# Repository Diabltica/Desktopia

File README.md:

# Desktopia

Desktopia is an open-source project for easy height control of your IKEA Skarsta/Trotten sit-stand desk, providing a
comfortable and customizable workspace experience.

A DC motor replaces the crank handle. Two boards control it: the **motherboard** under the desk top, and the **HMI board**
on the front edge with a round screen and five buttons. A time-of-flight sensor measures the desk height, so the desk can
go back to three saved heights at the press of a button.

## How it works

```mermaid
flowchart LR
    PSU[24 V power supply] -->|J1| MB
    subgraph MB[Motherboard - ATmega32U4]
        direction TB
        SHUNT[2 mΩ shunt + INA226]
        SW[P-MOSFET supply switch]
        TOF[VL53L1CB height sensor]
    end
    MB -->|J5: switched 24 V| DRV[Cytron MD10C motor driver]
    MB -->|J6: DIR + PWM + GND| DRV
    DRV --> MOTOR[Motor] --> GEAR[Gearbox] --> DESK[Desk]
    MB <-->|RJ11 cord: 5 V + RS-485| HMI[HMI board - RP2040<br/>round screen + 5 buttons]
```

- The **motherboard** makes every decision. It reads the height (VL53L1CB), runs the state machine, drives the motor
  driver (direction + PWM, with ramps) and stores the presets in its EEPROM. It also switches the driver's 24 V supply:
  on for a move, off after 5 minutes without one, and off at once if the motor current goes over the limit (INA226).
- The **HMI board** only displays what the motherboard sends and reports the button levels. It is powered by the
  motherboard through the RJ11 cord, which also carries the RS-485 link (250 kbaud, polled every 10 ms).
- If the cord, the sensor or the firmware fails, or the motor draws too much current, the motor stops: see the protections in
  [firmware/README.md](firmware/README.md#built-in-protections).

## Usage

| Action | Result |
|---|---|
| **Up / Down** held | the desk moves as long as the button is held |
| **Preset 1-3**, short press | the desk goes to the saved height |
| **Preset 1-3**, long press (2 s) | the current height is saved |
| any button during an automatic move | stop |

## Repository layout

| Folder | Content | Documentation |
|---|---|---|
| [hardware/desktopia/](hardware/desktopia/) | motherboard KiCad project (schematic, PCB) | [README](hardware/desktopia/README.md) |
| [hardware/desktopia_HMI/](hardware/desktopia_HMI/) | HMI board KiCad project (schematic, PCB) | [README](hardware/desktopia_HMI/README.md) |
| [hardware/kicad_library/](hardware/kicad_library/) | symbols and footprints shared by both KiCad projects (`JLCImport`, ...) | |
| [hardware/render.sh](hardware/render.sh) | renders the schematic / PCB / 3D images of the board READMEs; run by the [*Hardware images*](.github/workflows/hardware-images.yml) workflow on every push | |
| [firmware/desktopia/](firmware/desktopia/) | motherboard firmware (ATmega32U4, PlatformIO) | [README](firmware/desktopia/README.md) |
| [firmware/desktopia_HMI/](firmware/desktopia_HMI/) | HMI board firmware (RP2040, PlatformIO) | [README](firmware/desktopia_HMI/README.md) |
| [firmware/shared/hmi_link/](firmware/shared/hmi_link/) | link protocol and screen model, compiled into both firmwares | [hmi_protocol.h](firmware/shared/hmi_link/hmi_protocol.h) |
| [firmware/sim/](firmware/sim/) | PC simulation of both boards from their real sources (Linux / WSL) | [README](firmware/README.md#simulation-bench-optional) |
| [mechanical/](mechanical/) | 3D-printed motor supports with silent blocks and jaw coupling (CadQuery scripts, STL / STEP, assembly report) | [README](mechanical/README.md) |
| [documentation/](documentation/) | VL53L1X datasheet | |

## Getting started

Tools: [KiCad 10](https://www.kicad.org/) for the boards, [PlatformIO](https://platformio.org/) for the firmwares.

1. **Boards**: open each KiCad project, update the PCB from the schematic and order it. Every assembled part has its
   JLCPCB / LCSC number in the `LCSC` field. Read the board READMEs first: both PCBs still have to be updated after
   the latest schematic changes.
2. **HMI firmware**: `cd firmware/desktopia_HMI && pio run -t upload` with the board in USB boot mode.
3. **Motherboard firmware**: `cd firmware/desktopia && pio run -t upload` (the board must be powered from its 24 V input).
4. **First power-up**: follow [the checklist](firmware/README.md#first-power-up-do-it-in-this-order), with the motor
   decoupled from the desk at first.

The firmware of both boards can be tested on a PC without any hardware (`firmware/sim/`, Linux / WSL).

## Status

- Firmwares: build with no warnings; tested in the PC simulation only.
- Schematics: ERC checked, netlists checked by script.
- PCBs: **not yet updated** to the latest schematics (RJ11 link, RP2040 HMI board, power input, current sensor, motor supply switch).
- Nothing has been tested on real boards yet.

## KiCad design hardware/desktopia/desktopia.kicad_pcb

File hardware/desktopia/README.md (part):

# Desktopia – motherboard

KiCad 10 project: `desktopia.kicad_sch`, `desktopia.kicad_pcb`. Firmware: [../../firmware/desktopia/](../../firmware/desktopia/README.md).

The motherboard sits under the desk top. It takes the 24 V supply and passes it through a current shunt and a MOSFET
switch to its own H-bridge (DRV8701E gate driver, four N-MOSFETs), which drives the motor. The bridge can be bypassed:
J5 / J6 still give the switched 24 V and DIR / PWM to an external driver. The board measures the height, powers the HMI
board and talks to it.

## Views

Interactive viewer (KiCanvas, opens the files of the `main` branch in the browser):
[schematic](https://kicanvas.org/?github=https://github.com/Diabltica/Desktopia/blob/main/hardware/desktopia/desktopia.kicad_sch) · [PCB](https://kicanvas.org/?github=https://github.com/Diabltica/Desktopia/blob/main/hardware/desktopia/desktopia.kicad_pcb).

The images below are rendered by [`../render.sh`](../render.sh) and committed by the
[*Hardware images*](../../.github/workflows/hardware-images.yml) workflow on every push that touches `hardware/`.
Click an image to open it full size.
The 3D view shows the plugs of J1 / J5 / J6 / J7 in their headers: the `Desktopia:PluggableHeader_*` footprints carry
KiCad's Phoenix Contact header model and a plug generated by
[`pluggable_plug_3d.py`](../kicad_library/pcb/tools/pluggable_plug_3d.py) (the footprints by
[`pluggable_header_fp.py`](../kicad_library/pcb/tools/pluggable_header_fp.py)).

Reading the schematic: connections are drawn as wires. A label only appears where a net leaves one block for another,
at the MCU pin and at the block it reaches (`TOF_INT`, `SCL`, `SDA`, `Mpwm`, `Mdir`, `nSLEEP`, `nFAULT`, `MOTOR_PWR`,
`I_ALERT`, `RESET`, `+5V_HMI`, `MOTOR_SW`). `MOTOR_24V` only names a 15 A net. In the H-bridge block, `OUT1` / `OUT2`
join the two legs to J7, `LS_SRC` joins the low-side sources to the shunts R27 / R28 under U7, and `VM` names the
bridge supply after JP6. Wires that cross without a dot are not connected: MISO over SCK / MOSI at J2, D+ over D- at
the USB connector, Vin+ over Vin- at the INA226, DI over DE at U5.

Colours: each block has its own background and title colour (24 V input and 5 V supply, MCU, height sensor, HMI link,
motor supply, H-bridge). Wires and labels take the colour of their net class, with a legend on the sheet, left of the
MCU:

| Colour | Net class | Nets |
|---|---|---|
| red, thick | `Power_24V` | `+24V`, `MOTOR_24V`, `MOTOR_SW`, `VM`, `OUT1` / `OUT2`, `LS_SRC`: the 15 A path |
| orange | `Power_5V` | `+5V`, `+5V_HMI` |
| purple | `Power_2V8` | `+2V8` |
| grey | `GND` | `GND` |
| blue | `Motor_command` | `Mdir`, `Mpwm`, `nSLEEP`, `nFAULT`, `MOTOR_PWR`, `I_ALERT`, and PH / EN / nSLEEP / nFAULT after JP2-JP5 |
| magenta | `Gate_drive` | the four gates of the H-bridge |
| brown | `Current_sense` | Kelvin lines: Vin+ / Vin- of the INA226, SP / SN of the DRV8701 |
| teal | `Buses` | I2C (both sides of Q1 / Q2), ToF interrupt, RS-485, USB D+ / D- |
| green | `Default` | everything else |
| green (PCB only) | `HV_signal`, `Switch_node` | 24-38 V low-current nets (charge pump, bootstrap, Q5 gate), TPS5430 switch node |

The classes and their net patterns are in the project settings (*Schematic Setup → Net Classes*). Unnamed nets are
matched by their KiCad name (`Net-(Q6-G)`...): after renaming one of these parts, update its pattern. Each class also
sets the PCB track width, clearance and via: see *PCB rules*.

**Schematic**

**PCB**

| Front | Back (mirrored) |
|---|---|
|  |  |

**3D**

| Top | Bottom |
|---|---|
|  |  |

## Blocks

| Block | Parts | Notes |
|---|---|---|
| 24 V input | J1 (5.08 mm pluggable terminal, 15 A), D2 SMBJ28A (600 W TVS), C6 (100 µF 50 V bulk), C5 (10 µF 50 V ceramic), TP5 | J1 carries the full motor current. D2 clamps motor and hot-plug spikes below the 40 V absolute maximum of U2 and U6 |
| 24 V → 5 V | U2 TPS5430 (3 A buck), L1 22 µH (1.8 A, shielded), D1 SS34 (3 A), C3 10 nF (boot), C7 + C8 (2 × 47 µF ceramic), R4 / R7 (10k / 3.3k → 4.92 V), C4 / R9 / C12 / C11 (compensation) | 1.5 A available. ENA left open, see *Known issues* |
| Motor current | R23 2 mΩ 3 W shunt, U6 INA226 (I2C 0x40), C22, R25, C23 | ±41 A full scale; alert on PE6 / INT6 (R25 4.7k pull-up, C23 100 pF against motor spikes). The firmware cuts the PWM and Q5 on an alert |
| Motor supply switch | Q5 IPD90P04P4-05 (P-MOSFET, −40 V, 4.7 mΩ, TO-252), Q4 BSS138 (gate driver), R21 / R20 100k (gate divider), R22 10k (pull-down), D3 BZT52C15 (V<sub>GS</sub> clamp), C21 100 nF 50 V (soft start), D4 SS34, TP13 | no relay. `MOTOR_PWR` (PD7) high → Q4 on → V<sub>GS</sub> −12 V → J5 powered. R22 keeps it off while the MCU is in reset or blank. See *Power* |
| MCU | U4 ATmega32U4 @ 16 MHz (Y1, C15 / C16), RST1 reset button, R12 reset pull-up | Caterina bootloader, USB. HWB (PE2) is not connected: the Leonardo fuses leave HWBE off |
| USB | J3 USB-C (G-Switch GT-USB-7010ASV), R13 / R15 22 Ω, R18 / R19 5.1k on CC | VBUS only goes to the MCU's VBUS sense pin: USB does **not** power the board |
| ISP | J2 2×3 header (not assembled) | blank chip: bootloader + fuses with a USBasp |
| Height sensor | U3 VL53L1CB, U1 XC6206P282 (2.8 V LDO), Q1 / Q2 / Q3 BSS138 (5 V ↔ 2.8 V level shifters: SCL, SDA, GPIO1), R2 / R6 / R8 / R11, R10 | XSHUT tied high (R8). GPIO1 (data ready) reaches PB4 / PCINT4 as `TOF_INT` |
| Motor command | J5 (switched 24 V out, `MOTOR_SW`), J6 (DIR, PWM, GND), R26 / R24 (10k pull-downs on PWM / DIR) | DIR / PWM go to the on-board H-bridge, and to J6 for an external driver (Cytron MD10C R3) when the bridge is bypassed. The pull-downs keep the motor stopped while the MCU is in reset, in the bootloader or blank |
| H-bridge | U7 DRV8701E (gate driver, PH/EN), Q6 / Q7 / Q8 / Q9 BSC028N06NS (60 V, 2.8 mΩ, SuperSO8), C24 / C25 (2 × 470 µF 50 V low impedance), C26 / C27 (10 µF 50 V), C28 (100 nF, VM), C29 (VCP), C30 (charge pump), C31 / C32 (AVDD / DVDD), R27 / R28 (2 × 2 mΩ 3 W shunt, Kelvin), R29 / R30 (VREF divider), TP14 (SO), J7 (motor), JP2-JP5 (solder jumpers), JP6 (wire link) | PH = `Mdir`, EN = `Mpwm` (up to 100 kHz, 25 kHz planned). EN low = brake. `nSLEEP` (PB5) low = bridge off, `nFAULT` (PB7) = fault. Current limited cycle by cycle at about 14.6 A. See *H-bridge* |
| HMI link | J4 RJ11 6P6C, U5 SP485EEN (RS-485), F1 500 mA PTC, R14 / R17 4.7k bias, R16 120 Ω (not assembled), C18 / C20 | see the link section of the firmware README |
| Power LED | LED1, R3 (470 Ω, 6 mA), JP1 solder jumper | LED off until JP1 is bridged |

## Connectors

| Ref | Function | Pin-out |
|---|---|---|
| J1 | 24 V supply input | 1 = +24 V, 2 = GND |
| J2 | ISP | 1 = MISO, 2 = +5 V, 3 = SCK, 4 = MOSI, 5 = RESET, 6 = GND |
| J3 | USB-C: flashing and debug logs | USB 2.0 full speed |
| J4 | RJ11 cord to the HMI board | 1 = +5 V, 2 = GND, 3 = A, 4 = B, 5 = GND, 6 = +5 V |
| J5 | supply out to an external motor driver (after the shunt and Q5) | 1 = MOTOR_SW, 2 = GND |
| J6 | external motor driver command | 1 = DIR (`Mdir`, PC6), 2 = PWM (`Mpwm`, PB6 / OC1B), 3 = GND (the driver's logic ground) |
| J7 | motor, from the on-board H-bridge | 1 = OUT1 (Q6 / Q7), 2 = OUT2 (Q8 / Q9) |

The J4 pin-out is symmetric, so a reversed telephone cord only swaps A and B, never +5 V and GND. The HMI firmware
detects and corrects the swap. Use 6-conductor (6P6C) cords only, and never plug J4 into a telephone wall socket.

The four terminals unplug. The board has the header; the wires are screwed into a plug, so the board can be fitted or
removed without touching a screw under the desk. JLCPCB solders the headers; buy the plugs with the parts (LCSC), they
are not in the assembly BOM. Each header carries its plug in the `Plug` field of the schematic.

| Ref | Header (on the board) | Plug (on the cable) | Rating | Wire |
|---|---|---|---|---|
| J1, J5 | Cixi Kefa KF2EDGRC-5.08-2P (C441236), 5.08 mm, right angle, closed ends | KF2EDGK-5.08-2P-AA (C440880) | 15 A, 300 V | up to 2.5 mm² (12 AWG) |
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
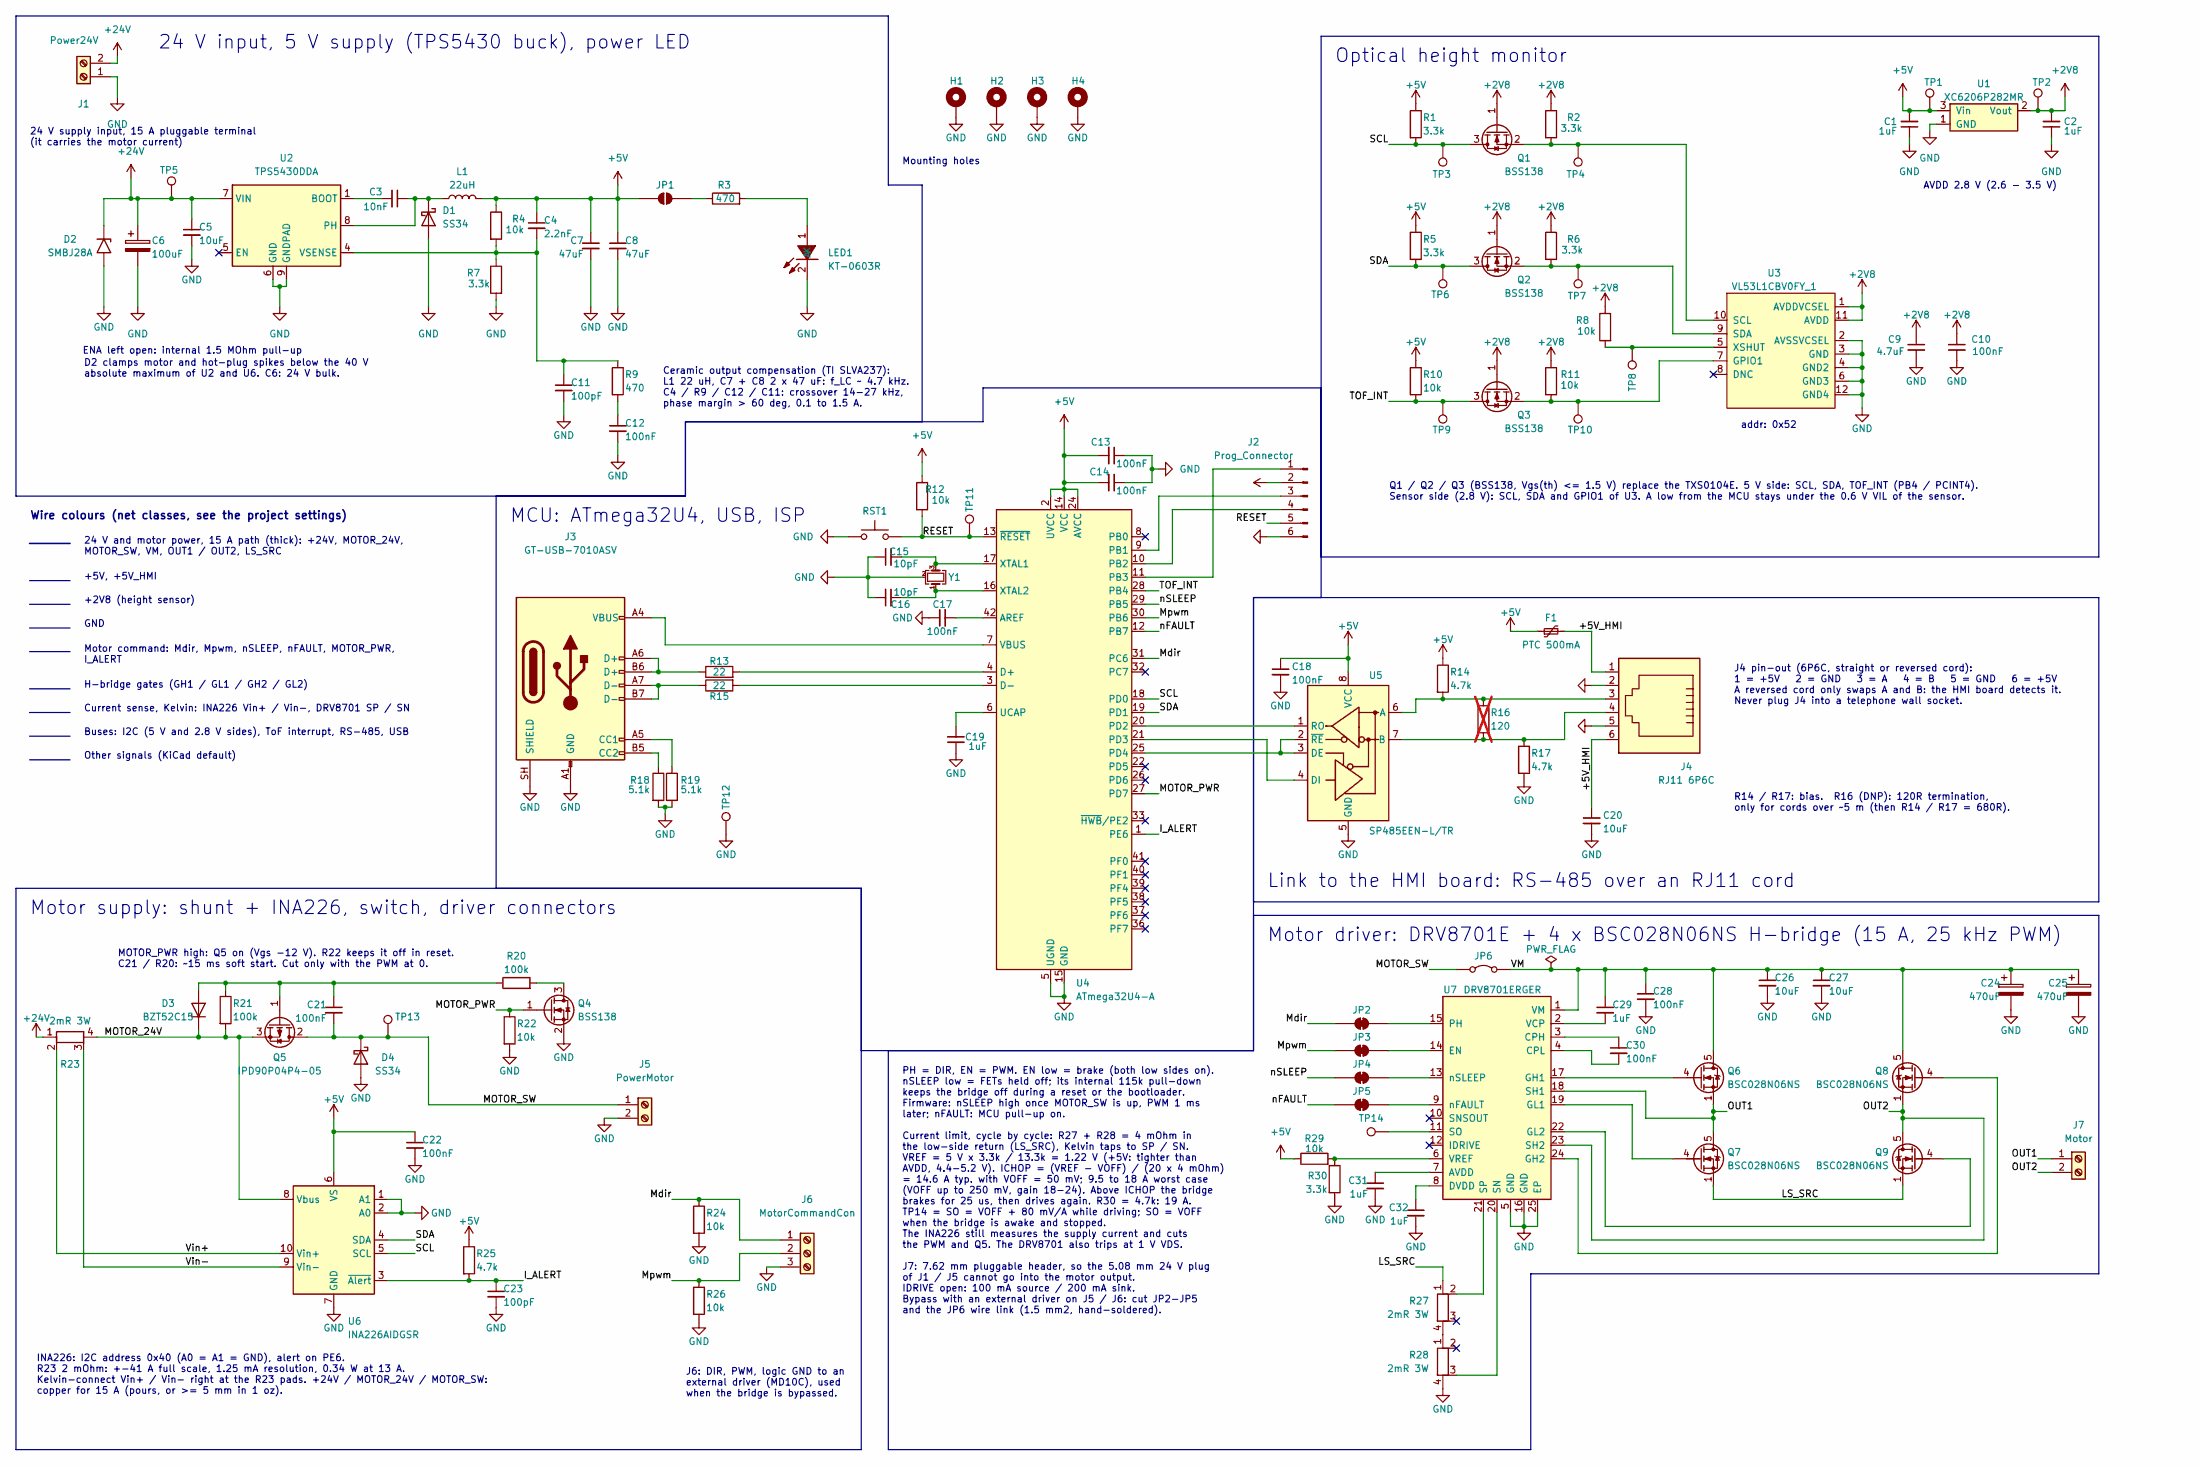
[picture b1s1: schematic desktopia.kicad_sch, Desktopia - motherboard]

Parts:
C1, C2, C19, C29, C31, C32: 1uF; C_0402_1005Metric; jlcpcb PartNumber C52923
C3: 10nF; C_0402_1005Metric; jlcpcb PartNumber C15195
C4: 2.2nF; C_0603_1608Metric; Manufacturer Part 0603B222K500NT; LCSC C1604
C5, C26, C27: 10uF; C_1206_3216Metric; Voltage 50V X5R; LCSC C13585
C6: 100uF; CP_Elec_8x10; Voltage 50V; Manufacturer Part RVT1H101M0810; LCSC C970687
C7, C8: 47uF; C_1206_3216Metric; Voltage 10V X5R; Manufacturer Part CL31A476MPHNNNE; LCSC C96123
C9: 4.7uF; C_0402_1005Metric; jlcpcb PartNumber C23733
C10, C13, C14, C17, C18: 100nF; C_0402_1005Metric; jlcpcb PartNumber C1525
C11, C23: 100pF; C_0402_1005Metric; Manufacturer Part 0402CG101J500NT; LCSC C1546
C12: 100nF; C_0402_1005Metric; Manufacturer Part CL05B104KO5NNNC; LCSC C1525
C15, C16: 10pF; C_0402_1005Metric; jlcpcb PartNumber C32949
C20: 10uF; C_0603_1608Metric; jlcpcb PartNumber C19702
C21, C28, C30: 100nF; C_0402_1005Metric; Voltage 50V X7R; Manufacturer Part CL05B104KB54PNC; LCSC C307331
C22: 100nF; C_0402_1005Metric; LCSC C1525
C24, C25: 470uF; CP_Radial_D10.0mm_P5.00mm; Voltage 50V; Manufacturer Part 50ZLJ470M10X20; LCSC C2902875
D1: SS34; D_SMA; jlcpcb PartNumber C8678
D2: SMBJ28A; D_SMB; Manufacturer Part SMBJ28A; LCSC C19077582
D3: BZT52C15; D_SOD-123; Manufacturer Part BZT52C15; LCSC C19077412
D4: SS34; D_SMA; Manufacturer Part SS34; LCSC C8678
F1: PTC 500mA; Fuse_1206_3216Metric; LCSC C720075
H1, H2, H3, H4: MountingHole_Pad; MountingHole_2.2mm_M2_Pad
J1: Power24V; PluggableHeader_2EDGRC_1x02_P5.08mm_Horizontal; Manufacturer Part KF2EDGRC-5.08-2P; LCSC C441236
J2: Prog_Connector; IDC-Header_2x03_P2.54mm_Vertical
J3: GT-USB-7010ASV; USB_C_Receptacle_G-Switch_GT-USB-7010ASV; Manufacturer Part GT-USB-7010ASV; LCSC C2988369
J4: RJ11 6P6C; RJ12_Amphenol_54601-x06_Horizontal; LCSC C3097716
J5: PowerMotor; PluggableHeader_2EDGRC_1x02_P5.08mm_Horizontal; Manufacturer Part KF2EDGRC-5.08-2P; LCSC C441236
J6: MotorCommandCon; PluggableHeader_15EDGRC_1x03_P3.81mm_Horizontal; Manufacturer Part WJ15EDGRC-3.81-03P-14-00A; LCSC C8406
J7: Motor; PluggableHeader_2EDGRC_1x02_P7.62mm_Horizontal; Manufacturer Part KF2EDGRC-7.62-2P; LCSC C441246
JP1: SolderJumper_2_Open; SolderJumper-2_P1.3mm_Open_TrianglePad1.0x1.5mm
JP2, JP3, JP4, JP5: SolderJumper_2_Bridged; SolderJumper-2_P1.3mm_Bridged_RoundedPad1.0x1.5mm
JP6: 1.5 mm2 wire; SolderWire-1.5sqmm_1x02_P6mm_D1.7mm_OD3mm
L1: 22uH; L_Sunlord_SWPA6045S; Manufacturer Part SWPA6045S220MT; jlcpcb PartNumber C83454
LED1: KT-0603R; Manufacturer Part KT-0603R; LCSC C2286
Q1, Q2, Q3, Q4: BSS138; SOT-23; Manufacturer Part BSS138; LCSC C7420339
Q5: IPD90P04P4-05; TO-252-2; Manufacturer Part IPD90P04P405; LCSC C536914
Q6, Q7, Q8, Q9: BSC028N06NS; TDSON-8-1; Manufacturer Part BSC028N06NSATMA1; LCSC C148250
R1, R2, R5, R6, R7, R30: 3.3k; R_0402_1005Metric; jlcpcb PartNumber C25890
R3: 470; R_0402_1005Metric; jlcpcb PartNumber C25117
R4, R8, R11, R12: 10k; R_0402_1005Metric; jlcpcb PartNumber C25744
R9: 470; R_0402_1005Metric; Manufacturer Part 0402WGF4700TCE; LCSC C25117
R10, R22, R24, R26, R29: 10k; R_0402_1005Metric; Manufacturer Part 0402WGF1002TCE; LCSC C25744
R13, R15: 22; R_0402_1005Metric; jlcpcb PartNumber C25092
R14, R17: 4.7k; R_0402_1005Metric; jlcpcb PartNumber C25900
R16: 120; R_0402_1005Metric; jlcpcb PartNumber C25079; not fitted
R18, R19: 5.1k; R_0402_1005Metric; jlcpcb PartNumber C25905
R20, R21: 100k; R_0402_1005Metric; Manufacturer Part 0402WGF1003TCE; LCSC C25741
R23, R27, R28: 2mR 3W; R_2512_CurrentSensing_opti; LCSC C154685
R25: 4.7k; R_0402_1005Metric; LCSC C25900
RST1: TS-1088-AR02016; SW_SPST_TS-1088-xR020; LCSC C720477
TP1, TP2, TP3, TP4, TP5, TP6, TP7, TP8, TP9, TP10, TP11, TP12, TP13, TP14: TestPoint; TestPoint_Pad_D1.0mm
U1: XC6206P282MR; SOT-23-3; Manufacturer Part XC6206P282MR; LCSC C347374
U2: TPS5430DDA; TI_SO-PowerPAD-8_ThermalVias; jlcpcb PartNumber C9864
U3: VL53L1CBV0FY_1; Manufacturer Part VL53L1CBV0FY/1; LCSC C2970716
U4: ATmega32U4-A; TQFP-44_10x10mm_P0.8mm; LCSC C44854
U5: SP485EEN-L/TR; SOIC-8_3.9x4.9mm_P1.27mm; LCSC C6855
U6: INA226AIDGSR; TSSOP-10_3x3mm_P0.5mm; LCSC C49851
U7: DRV8701ERGER; Texas_RGE0024H_VQFN-24-1EP_4x4mm_P0.5mm_EP2.7x2.7mm_Thermal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; Manufacturer Part DRV8701ERGER; LCSC C90964
Y1: X322516MLB4SI; Crystal_SMD_3225-4Pin_3.2x2.5mm; jlcpcb PartNumber C13738

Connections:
+2V8: C2.2, C9.1, C10.1, Q1.1 (G), Q2.1 (G), Q3.1 (G), R2.1, R6.1, R8.1, R11.1, TP2.1 (1_1), U1.2 (Vout), U3.1 (AVDDVCSEL), U3.11 (AVDD)
+5V: C1.2, C4.1, C7.1, C8.1, C13.2, C14.2, C18.1, C22.1, F1.1, J2.2, JP1.1 (A), L1.2, R1.1, R4.1, R5.1, R10.1, R12.1, R14.1, R25.1, R29.1, TP1.1 (1_1), U1.3 (Vin), U4.2 (UVCC), U4.14 (VCC), U4.24 (AVCC), U4.34 (VCC), U4.44 (AVCC), U5.8 (VCC), U6.6 (VS)
+24V: C5.1, C6.1, D2.1 (A1), J1.2, R23.1, TP5.1 (1_1), U2.7 (VIN)
/+5V_HMI: C20.1, F1.2, J4.1, J4.6
/I_ALERT: C23.1, R25.2, U4.1 (PE6), U6.3 (~Alert)
/LS_SRC: Q7.1 (S), Q7.2 (S), Q7.3 (S), Q9.1 (S), Q9.2 (S), Q9.3 (S), R27.1
/MOTOR_24V: D3.1 (K), Q5.3 (S), R21.2, R23.4, U6.8 (Vbus)
/MOTOR_PWR: Q4.1 (G), R22.1, U4.27 (PD7)
/MOTOR_SW: C21.2, D4.1 (K), J5.1, JP6.1 (A), Q5.2 (D), TP13.1 (1_1)
/Mdir: J6.1, JP2.1 (A), R24.1, U4.31 (PC6)
/Mpwm: J6.2, JP3.1 (A), R26.1, U4.30 (PB6)
/OUT1: J7.1, Q6.1 (S), Q6.2 (S), Q6.3 (S), Q7.5 (D), U7.18 (SH1)
/OUT2: J7.2, Q8.1 (S), Q8.2 (S), Q8.3 (S), Q9.5 (D), U7.23 (SH2)
/RESET: J2.5, R12.2, RST1.2, TP11.1 (1_1), U4.13 (~RESET)
/SCL: Q1.3 (D), R1.2, TP3.1 (1_1), U4.18 (PD0), U6.5 (SCL)
/SDA: Q2.3 (D), R5.2, TP6.1 (1_1), U4.19 (PD1), U6.4 (SDA)
/TOF_INT: Q3.3 (D), R10.2, TP9.1 (1_1), U4.28 (PB4)
/Vin+: R23.2, U6.10 (Vin+)
/Vin-: R23.3, U6.9 (Vin-)
/nFAULT: JP5.1 (A), U4.12 (PB7)
/nSLEEP: JP4.1 (A), U4.29 (PB5)
GND: C1.1, C2.1, C5.2, C6.2, C7.2, C8.2, C9.2, C10.2, C11.2, C12.2, C13.1, C14.1, C15.1, C16.1, C17.1, C18.2, C19.1, C20.2, C22.2, C23.2, C24.2, C25.2, C26.2, C27.2, C28.2, C31.2, C32.2, D1.2 (A), D2.2 (A2), D4.2 (A), H1.1 (1_1), H2.1 (1_1), H3.1 (1_1), H4.1, J1.1, J2.6, J3.A1 (GND), J3.A12 (GND), J3.B1 (GND), J3.B12 (GND), J3.SH (SHIELD), J4.2, J4.5, J5.2, J6.3, LED1.2 (K), Q4.2 (S), R7.2, R17.2, R18.2, R19.2, R22.2, R24.2, R26.2, R28.4, R30.2, RST1.1, TP12.1 (1_1), U1.1 (GND), U2.6 (GND), U2.9 (GNDPAD), U3.2 (AVSSVCSEL), U3.3 (GND), U3.4 (GND2), U3.6 (GND3), U3.12 (GND4), U4.5 (UGND), U4.15 (GND), U4.23 (GND), U4.35 (GND), U4.43 (GND), U5.5 (GND), U6.1 (A1), U6.2 (A0), U6.7 (GND), U7.5 (GND), U7.16 (GND), U7.25 (EP), Y1.2 (G), Y1.4 (G)
unnamed: C12.1, R9.2
unnamed: C3.1, D1.1 (K), L1.1, U2.8 (PH)
unnamed: C21.1, D3.2 (A), Q5.1 (G), R20.1, R21.1
unnamed: J2.1, U4.11 (PB3)
unnamed: J2.3, U4.9 (PB1)
unnamed: J2.4, U4.10 (PB2)
unnamed: J3.A5 (CC1), R19.1
unnamed: J3.B5 (CC2), R18.1
unnamed: J3.A6 (D+), J3.B6 (D+), R13.1
unnamed: J3.A7 (D-), J3.B7 (D-), R15.1
unnamed: JP1.2 (B), R3.1
unnamed: JP2.2 (B), U7.15 (PH)
unnamed: JP3.2 (B), U7.14 (EN)
unnamed: JP4.2 (B), U7.13 (nSLEEP)
unnamed: JP5.2 (B), U7.9 (nFAULT)
unnamed: C24.1, C25.1, C26.1, C27.1, C28.1, C29.1, JP6.2 (B), Q6.5 (D), Q8.5 (D), U7.1 (VM)
unnamed: LED1.1 (A), R3.2
unnamed: Q1.2 (S), R2.2, TP4.1 (1_1), U3.10 (SCL)
unnamed: Q2.2 (S), R6.2, TP7.1 (1_1), U3.9 (SDA)
unnamed: Q3.2 (S), R11.2, TP10.1 (1_1), U3.7 (GPIO1)
unnamed: Q4.3 (D), R20.2
unnamed: Q6.4 (G), U7.17 (GH1)
unnamed: Q7.4 (G), U7.19 (GL1)
unnamed: Q8.4 (G), U7.24 (GH2)
unnamed: Q9.4 (G), U7.22 (GL2)
unnamed: R27.4, R28.1
unnamed: C3.2, U2.1 (BOOT)
unnamed: C4.2, C11.1, R4.2, R7.1, R9.1, U2.4 (VSENSE)
unnamed: R8.2, TP8.1 (1_1), U3.5 (XSHUT)
unnamed: C17.2, U4.42 (AREF)
unnamed: R13.2, U4.4 (D+)
unnamed: R15.2, U4.3 (D-)
unnamed: U4.20 (PD2), U5.1 (RO)
unnamed: U4.21 (PD3), U5.4 (DI)
unnamed: U4.25 (PD4), U5.2 (~RE), U5.3 (DE)
unnamed: C19.2, U4.6 (UCAP)
unnamed: J3.A4 (VBUS), J3.A9 (VBUS), J3.B4 (VBUS), J3.B9 (VBUS), U4.7 (VBUS)
unnamed: C15.2, U4.17 (XTAL1), Y1.3
unnamed: C16.2, U4.16 (XTAL2), Y1.1
unnamed: J4.3, R14.2, R16.1, U5.6 (A)
unnamed: J4.4, R16.2, R17.1, U5.7 (B)
unnamed: C31.1, U7.7 (AVDD)
unnamed: C30.1, U7.3 (CPH)
unnamed: C30.2, U7.4 (CPL)
unnamed: C32.1, U7.8 (DVDD)
unnamed: R28.3, U7.20 (SN)
unnamed: TP14.1 (1_1), U7.11 (SO)
unnamed: R27.2, U7.21 (SP)
unnamed: C29.2, U7.2 (VCP)
unnamed: R29.2, R30.1, U7.6 (VREF)

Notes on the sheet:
J4 pin-out (6P6C, straight or reversed cord): 1 = +5V 2 = GND 3 = A 4 = B 5 = GND 6 = +5V A reversed cord only swaps A and B: the HMI board detects it. Never plug J4 into a telephone wall socket.
+2V8 (height sensor)
MCU: ATmega32U4, USB, ISP
24 V supply input, 15 A pluggable terminal (it carries the motor current)
Link to the HMI board: RS-485 over an RJ11 cord
J6: DIR, PWM, logic GND to an external driver (MD10C), used when the bridge is bypassed.
Current sense, Kelvin: INA226 Vin+ / Vin-, DRV8701 SP / SN
addr: 0x52
Q1 / Q2 / Q3 (BSS138, Vgs(th) <= 1.5 V) replace the TXS0104E. 5 V side: SCL, SDA, TOF_INT (PB4 / PCINT4). Sensor side (2.8 V): SCL, SDA and GPIO1 of U3. A low from the MCU stays under the 0.6 V VIL of the sensor.
Mounting holes
Motor supply: shunt + INA226, switch, driver connectors
H-bridge gates (GH1 / GL1 / GH2 / GL2)
24 V and motor power, 15 A path (thick): +24V, MOTOR_24V, MOTOR_SW, VM, OUT1 / OUT2, LS_SRC
Motor command: Mdir, Mpwm, nSLEEP, nFAULT, MOTOR_PWR, I_ALERT
Motor driver: DRV8701E + 4 x BSC028N06NS H-bridge (15 A, 25 kHz PWM)
AVDD 2.8 V (2.6 - 3.5 V)
D2 clamps motor and hot-plug spikes below the 40 V absolute maximum of U2 and U6. C6: 24 V bulk.
+5V, +5V_HMI
MOTOR_PWR high: Q5 on (Vgs -12 V). R22 keeps it off in reset. C21 / R20: ~15 ms soft start. Cut only with the PWM at 0.
INA226: I2C address 0x40 (A0 = A1 = GND), alert on PE6. R23 2 mOhm: +-41 A full scale, 1.25 mA resolution, 0.34 W at 13 A. Kelvin-connect Vin+ / Vin- right at the R23 pads. +24V / MOTOR_24V / MOTOR_SW: copper for 15 A (pours, or >= 5 mm in 1 oz).
Other signals (KiCad default)
Ceramic output compensation (TI SLVA237): L1 22 uH, C7 + C8 2 x 47 uF: f_LC ~ 4.7 kHz. C4 / R9 / C12 / C11: crossover 14-27 kHz, phase margin > 60 deg, 0.1 to 1.5 A.
R14 / R17: bias. R16 (DNP): 120R termination, only for cords over ~5 m (then R14 / R17 = 680R).
ENA left open: internal 1.5 MOhm pull-up
GND
PH = DIR, EN = PWM. EN low = brake (both low sides on). nSLEEP low = FETs held off; its internal 115k pull-down keeps the bridge off during a reset or the bootloader. Firmware: nSLEEP high once MOTOR_SW is up, PWM 1 ms later; nFAULT: MCU pull-up on. Current limit, cycle by cycle: R27 + R28 = 4 mOhm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
24 V input, 5 V supply (TPS5430 buck), power LED
Optical height monitor
Buses: I2C (5 V and 2.8 V sides), ToF interrupt, RS-485, USB
Wire colours (net classes, see the project settings)

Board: 2 copper layers, 117 parts (4 on the bottom side), 72 nets, no tracks yet.

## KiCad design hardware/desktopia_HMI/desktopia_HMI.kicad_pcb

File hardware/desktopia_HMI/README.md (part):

# Desktopia – HMI board

KiCad 10 project: `desktopia_HMI.kicad_sch`, `desktopia_HMI.kicad_pcb`. Firmware: [../../firmware/desktopia_HMI/](../../firmware/desktopia_HMI/README.md).

The HMI board sits on the front edge of the desk. It carries the round screen and the five buttons. Its own RP2040
draws the screen, debounces the buttons and answers the motherboard over RS-485. A single RJ11 cord brings both the
power and the link.

## Views

Interactive viewer (KiCanvas, opens the files of the `main` branch in the browser):
[schematic](https://kicanvas.org/?github=https://github.com/Diabltica/Desktopia/blob/main/hardware/desktopia_HMI/desktopia_HMI.kicad_sch) · [PCB](https://kicanvas.org/?github=https://github.com/Diabltica/Desktopia/blob/main/hardware/desktopia_HMI/desktopia_HMI.kicad_pcb).

The images below are rendered by [`../render.sh`](../render.sh) and committed by the
[*Hardware images*](../../.github/workflows/hardware-images.yml) workflow on every push that touches `hardware/`.
Click an image to open it full size.
The screen module model (`RoundLCD.wrl`) shows the real UI, taken from a screenshot of the simulator: it is generated by
[`round_lcd_3d.py`](../kicad_library/pcb/tools/round_lcd_3d.py) (rerun it after `firmware/sim/run.sh` to show another screen).
The picture is turned the way the firmware draws it for the module's position on the board (see J2 below).
The cord soldered to J3 (`Cable_6P6C_SolderPads.wrl`: about 1 cm of cord, the six wires, the solder joints and the
cable tie) is generated by [`cable_6p6c_3d.py`](../kicad_library/pcb/tools/cable_6p6c_3d.py).

Reading the schematic: every connection is a wire, with no labels. The parts sit next to the RP2040 pins they use:
the flash, crystal, USB, RUN and SWD on its left; the RS-485 transceiver, the buttons and the screen connector on its
right. Wires that cross without a dot are not connected: GPIO0 (to DI) over GPIO1 / GPIO2, and the screen CS (GPIO17)
over SCK / MOSI / DC, because the connector pin order differs from the GPIO order.
Each block has its own background and title colour (power and USB, RP2040 and flash, RS-485 link, buttons, screen).
Wires take the colour of their net class, as on the motherboard, with a legend at the bottom left of the sheet:
orange +5V, purple +3V3, pink +1V1, grey GND, teal the buses (USB, RS-485 and its UART, QSPI, screen SPI), green the
rest. See *PCB rules*.

**Schematic**

**PCB**

| Front | Back (mirrored) |
|---|---|
|  |  |

**3D**

| Top | Bottom |
|---|---|
|  |  |

## Blocks

| Block | Parts | Notes |
|---|---|---|
| MCU | U3 RP2040, Y1 12 MHz (C8 / C10 33 pF, R6 1k), decoupling C4-C7, C9, C11-C19 | standard Raspberry Pi minimal design |
| Flash | U2 W25Q128JVSIQ (16 MB QSPI) | the firmware uses 2 MB |
| 3.3 V | U1 XC6206P332 LDO, C1 / C2 (input), C3 (output) | supplies the RP2040, flash and transceiver |
| Link | J3 solder pads for the 6P6C cord, U4 SP3485EN (3.3 V RS-485), R8 120 Ω (not assembled) | UART0: GP0 TX, GP1 RX, GP2 DE + /RE |
| USB | J1 USB-C (G-Switch GT-USB-7010ASV), D1 SS14, R1 / R3 5.1k on CC, R4 / R2 22 Ω (D+ / D-) | bench flashing only |
| Boot / debug | SW1 BOOT (QSPI_SS through R5 1k), R7 10k RUN pull-up, TP1-TP4 SWD | no reset button: replug, or ground TP2 (RUN) |
| Screen | J2 7-pin connector, TP5-TP9 | GC9A01 240×240 round LCD on SPI0 |
| Buttons | SW2-SW6 Kailh Choc hot-swap sockets (PG1350) | to GND, internal pull-ups |

## Connectors

| Ref | Function | Pin-out |
|---|---|---|
| J1 | USB-C | flashing (UF2 bootloader) |
| J2 | round LCD | 1 = RST (GP21), 2 = CS (GP17), 3 = DC (GP20), 4 = MOSI (GP19), 5 = SCK (GP18), 6 = GND, 7 = +5 V |
| J3 | flat 6P6C cord to the motherboard, soldered (see below) | 1 = +5 V, 2 = GND, 3 = A, 4 = B, 5 = GND, 6 = +5 V |

J2 is numbered from the other end than the module's pin labels: the module's VCC, GND, SCL, SDA, DC, CS, RST are
J2 pins 7 down to 1.

The module sits with its pin header towards the buttons (J2 at 90°), turned 180° from the first layout: the firmware
turns the picture to match (`DISPLAY_ROTATION` 3 in `firmware/desktopia_HMI/include/hmi_config.h`).

Buttons: SW6 Up = GP11, SW5 Down = GP12, SW4 / SW3 / SW2 Preset 1 / 2 / 3 = GP13 / GP14 / GP15. On the PCB (front
view) they sit from SW2 on the left to SW6 on the right.

## The cord (J3)

The board sits at 45° under the front edge of the desk, in a wedge-shaped housing. An RJ11 jack would stand 12 mm
off the board, and its cord would leave parallel or perpendicular to the board, so at 45° to the desk either way.
The cord is therefore **soldered**: J3 (`Desktopia:Cable_6P6C_SolderPads`) has six 1 mm holes at 2.54 mm and two
slots for a 2.5 mm cable tie. The cord lies against the **bottom** of the board, leaves over the board edge (the
dashed *board edge* line on the Fab layer) and folds flat against the underside of the desk. Only the motherboard end
has an RJ11 plug, so the cord is unplugged there.

1. Take a flat 6-conductor cord (6P6C, sometimes sold as "RJ12") with a plug on one end, or crimp one.
   4-conductor cords (6P4C) do not work.
2. Strip about 10 mm of the jacket, strip and tin 3 mm of each wire.
3. Push the wires through the holes from the bottom and solder them on the top, **in their flat order**, edge wire
   on pad 1. Either direction is fine: the pin-out is symmetric, and
   a mirrored order only swaps A and B, which the firmware detects. Never cross two wires. The Fab layer shows the
   usual colours (white, black, red, green, yellow, blue), for reference only.
4. Put a cable tie through the two slots around the jacket, just behind the stripped end, its head under the cord.

## Power

- The motherboard supplies 5 V through the cord, limited by its 500 mA PTC. The screen module takes the 5 V and
  regulates its own 3.3 V. Its logic is driven at 3.3 V by the RP2040.
- On the bench, USB-C powers the board through the Schottky D1, which keeps the cord's 5 V out of the USB host.
  Unplug the cord at the motherboard while flashing over USB: otherwise the USB also feeds the motherboard's 5 V rail through the cord.

## Flashing

First flash: hold **SW1 (BOOT)**, plug the USB-C cable, then release SW1. The board appears as a USB drive (RPI-RP2).
Then run `pio run -t upload`, or copy `firmware.uf2` onto the drive. Later updates work the same way, or through SWD
on TP4 (SWCLK) / TP3 (SWDIO) / TP1 (GND).

## Test points

| TP | Net | TP | Net |
|---|---|---|---|
| TP1 | GND | TP6 | LCD_MOSI |
| TP2 | RUN (ground it to reset) | TP7 | LCD_DC |
| TP3 | SWDIO | TP8 | LCD_CS |
| TP4 | SWCLK | TP9 | LCD_RST |
| TP5 | LCD_SCK | | |

## Assembly (JLCPCB)

Every assembled part has its LCSC number in the `LCSC` and `jlcpcb PartNumber` fields, Basic parts first.

- Y1 is the Basic X322512MSB4SI (C9002). It is specified for a 20 pF load, hence the 33 pF capacitors C8 / C10.
- The Kailh Choc hot-swap sockets (CPG135001S30, C5333465) are out of stock at JLCPCB: solder them by hand.
- J1 is the G-Switch GT-USB-7010ASV (C2988369, $0.09). It replaces the HRO TYPE-C-31-M-12 ($0.19); the pins are the
  same, the footprint is KiCad's `USB_C_Receptacle_G-Switch_GT-USB-7010ASV`.
- U2 stays the W25Q128JVSIQ (16 MB) because it is a Basic part. The 2 MB and 4 MB Winbond parts are Extended at JLCPCB
  and cost $1.0 to $1.4. With the $3 loading fee, they only pay off from about 4 boards per order.
- The other extended parts are U3 (RP2040) and J1. Everything else is Basic.
- Not assembled: R8 (termination, only for cords over ~5 m) and the test points. J2 takes the screen module's
  cable.
- 3D model of J1: the LCSC one (`kicad_library/pcb/JLCImport.3dshapes`), as on the motherboard. R8 has its model but
  is marked DNP, so the 3D view hides it.

## PCB rules

The method and the sources are the motherboard's (see *PCB rules* in its [README](../desktopia/README.md)): 2 layers,
FR-4 1.6 mm, 1 oz (35 µm) copper, made by JLCPCB, track currents from IPC-2221 at ΔT 10 °C. Every net here is at 5 V
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
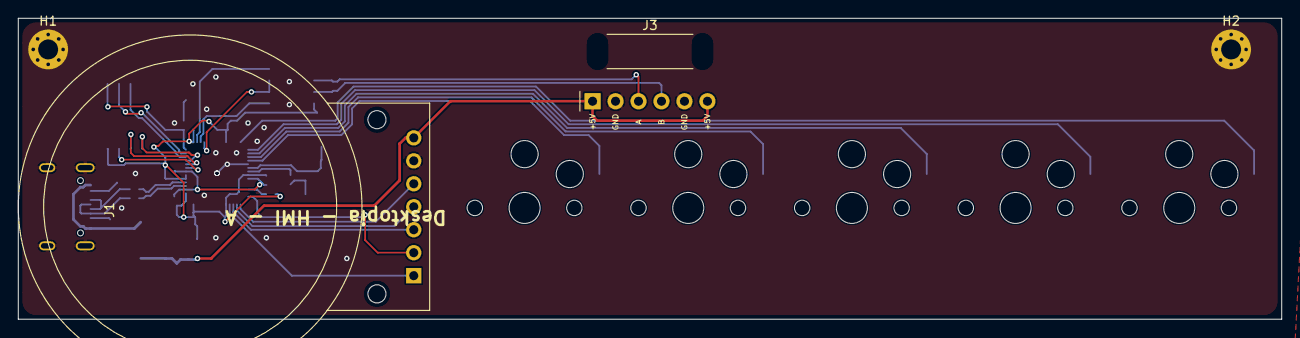
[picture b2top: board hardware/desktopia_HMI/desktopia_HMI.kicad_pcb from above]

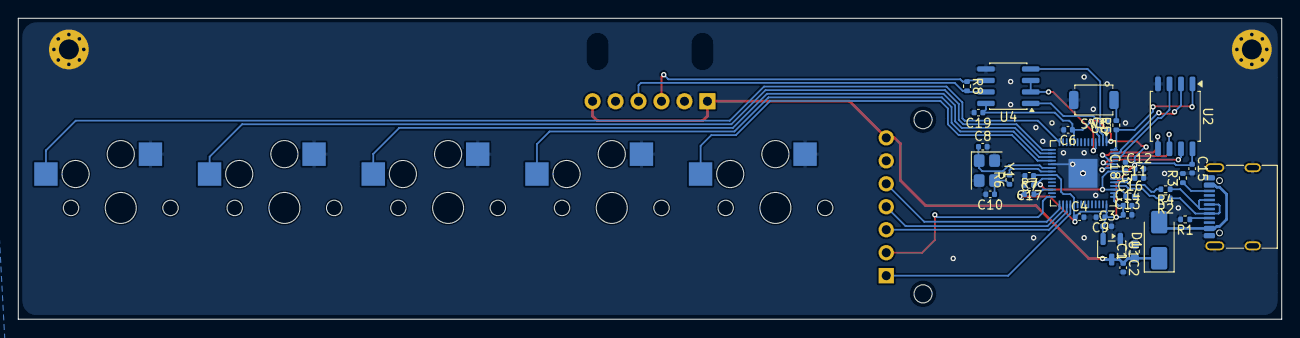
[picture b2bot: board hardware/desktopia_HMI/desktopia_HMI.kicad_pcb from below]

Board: 2 copper layers, 139.7 x 33.3 mm, 44 parts (35 on the bottom side), 37 nets.

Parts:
C1: 10uF; C_0603_1608Metric
C2, C3, C14, C16: 1uF; C_0402_1005Metric
C4, C5, C6, C7, C9, C11, C12, C13, C15, C17, C18, C19: 100nF; C_0402_1005Metric
C8, C10: 33pF; C_0402_1005Metric
D1: SS14; D_SMA
H1, H2: MountingHole_Pad; MountingHole_2.2mm_M2_Pad_Via
J1: GT-USB-7010ASV; USB_C_Receptacle_G-Switch_GT-USB-7010ASV
J2: LCD_Connector; LCD_round_screen
J3: 6P6C cord, soldered; Cable_6P6C_SolderPads
R1, R3: 5.1k; R_0402_1005Metric
R2, R4: 22; R_0402_1005Metric
R5, R6: 1k; R_0402_1005Metric
R7: 10k; R_0402_1005Metric
R8: 120; R_0402_1005Metric
SW1: TS-1088-AR02016; SW_SPST_TS-1088-xR020
SW2, SW3, SW4, SW5, SW6: SW_Push; PG1350
U1: XC6206P332MR; SOT-23-3
U2: W25Q128JVSIQ; SOIC-8_5.3x5.3mm_P1.27mm
U3: RP2040; QFN-56-1EP_7x7mm_P0.4mm_EP3.2x3.2mm
U4: SP3485EN-L/TR; SOIC-8_3.9x4.9mm_P1.27mm
Y1: 12MHz; Crystal_SMD_3225-4Pin_3.2x2.5mm

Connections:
+1V1: C16.1, C17.1, C18.1, U3.23 (DVDD), U3.45 (VREG_VOUT), U3.50 (DVDD)
+3V3: C3.1, C4.1, C5.1, C6.1, C7.1, C9.1, C11.1, C12.1, C13.1, C14.1, C15.1, C19.1, R7.1, U1.2 (VO), U2.8 (VCC), U3.1 (IOVDD), U3.10 (IOVDD), U3.22 (IOVDD), U3.33 (IOVDD), U3.42 (IOVDD), U3.43 (ADC_AVDD), U3.44 (VREG_VIN), U3.48 (USB_VDD), U3.49 (IOVDD), U4.8 (VCC)
+5V: C1.1, C2.1, D1.1 (K), J2.7, J3.1, J3.6, U1.3 (VI)
/D+: R4.2, U3.47 (USB_DP)
/D-: R2.2, U3.46 (USB_DM)
/data+: J3.4, R8.2, U4.7 (B)
/data-: J3.3, R8.1, U4.6 (A)
GND: C1.2, C2.2, C3.2, C4.2, C5.2, C6.2, C7.2, C8.2, C9.2, C10.2, C11.2, C12.2, C13.2, C14.2, C15.2, C16.2, C17.2, C18.2, C19.2, H1.1 (1_1), H2.1 (1_1), J1.A1 (GND), J1.A12 (GND), J1.B1 (GND), J1.B12 (GND), J1.SH (SHIELD), J2.6, J3.2, J3.5, R1.2, R3.2, SW1.2, SW2.1, SW3.1, SW4.1, SW5.1, SW6.1, U1.1 (GND), U2.4 (GND), U3.19 (TESTEN), U3.57 (GND), U4.5 (GND), Y1.2 (G), Y1.4 (G)
unnamed: C10.1, R6.1, Y1.3
unnamed: D1.2 (A), J1.A4 (VBUS), J1.A9 (VBUS), J1.B4 (VBUS), J1.B9 (VBUS)
unnamed: J1.A5 (CC1), R1.1
unnamed: J1.B5 (CC2), R3.1
unnamed: J1.A6 (D+), J1.B6 (D+), R4.1
unnamed: J1.A7 (D-), J1.B7 (D-), R2.1
unnamed: J2.1, U3.32 (GPIO21)
unnamed: J2.2, U3.28 (GPIO17)
unnamed: J2.3, U3.31 (GPIO20)
unnamed: J2.4, U3.30 (GPIO19)
unnamed: J2.5, U3.29 (GPIO18)
unnamed: R5.2, SW1.1
unnamed: U2.6 (CLK), U3.52 (QSPI_SCLK)
unnamed: U2.5 (DI/IO_{0}), U3.53 (QSPI_SD0)
unnamed: U2.2 (DO/IO_{1}), U3.55 (QSPI_SD1)
unnamed: R5.1, U2.1 (~CS), U3.56 (~QSPI_SS)
unnamed: U2.7 (~HOLD/~RESET/IO_{3}), U3.51 (QSPI_SD3)
unnamed: U2.3 (~WP/IO_{2}), U3.54 (QSPI_SD2)
unnamed: U3.2 (GPIO0), U4.4 (DI)
unnamed: U3.3 (GPIO1), U4.1 (RO)
unnamed: U3.4 (GPIO2), U4.2 (~RE), U4.3 (DE)
unnamed: SW6.2, U3.14 (GPIO11)
unnamed: SW5.2, U3.15 (GPIO12)
unnamed: SW4.2, U3.16 (GPIO13)
unnamed: SW3.2, U3.17 (GPIO14)
unnamed: SW2.2, U3.18 (GPIO15)
unnamed: R7.2, U3.26 (RUN)
unnamed: C8.1, U3.20 (XIN), Y1.1
unnamed: R6.2, U3.21 (XOUT)

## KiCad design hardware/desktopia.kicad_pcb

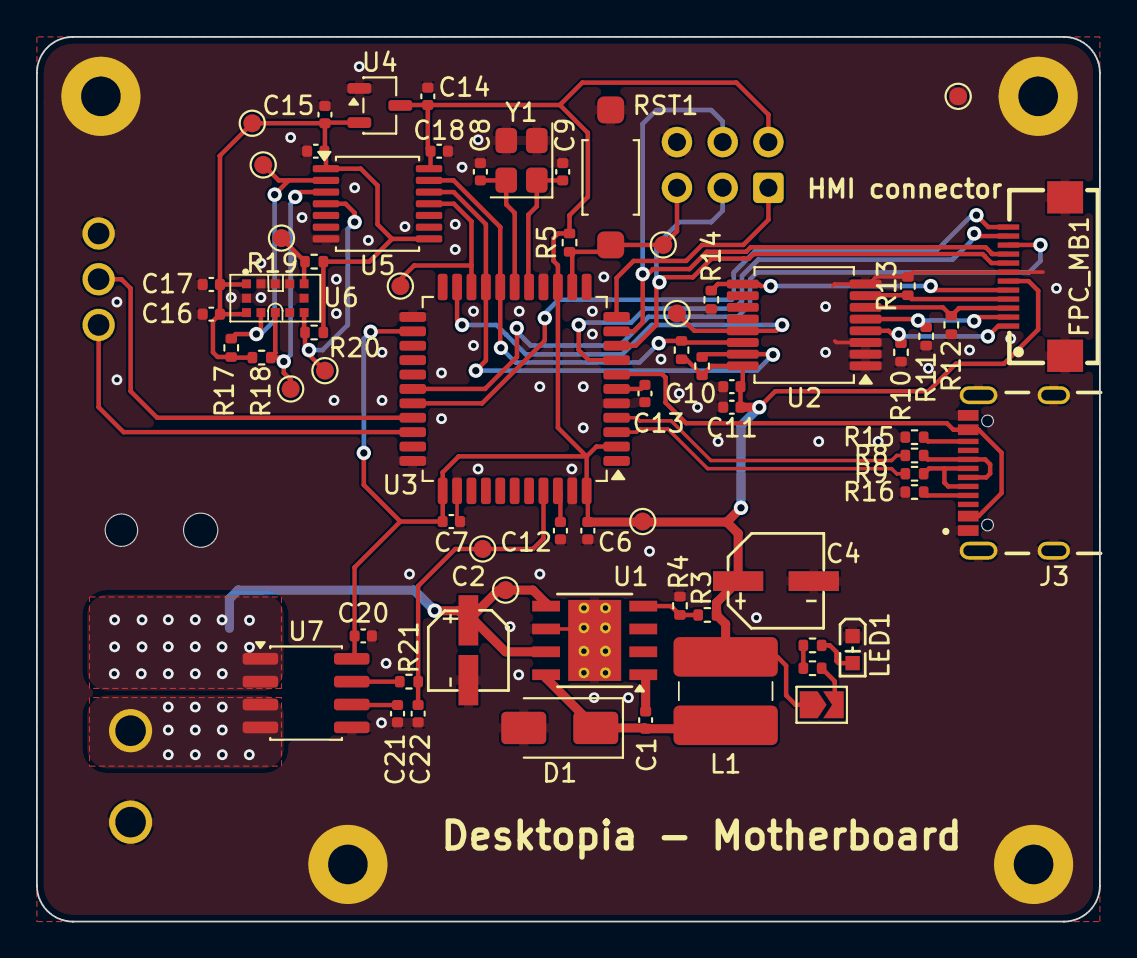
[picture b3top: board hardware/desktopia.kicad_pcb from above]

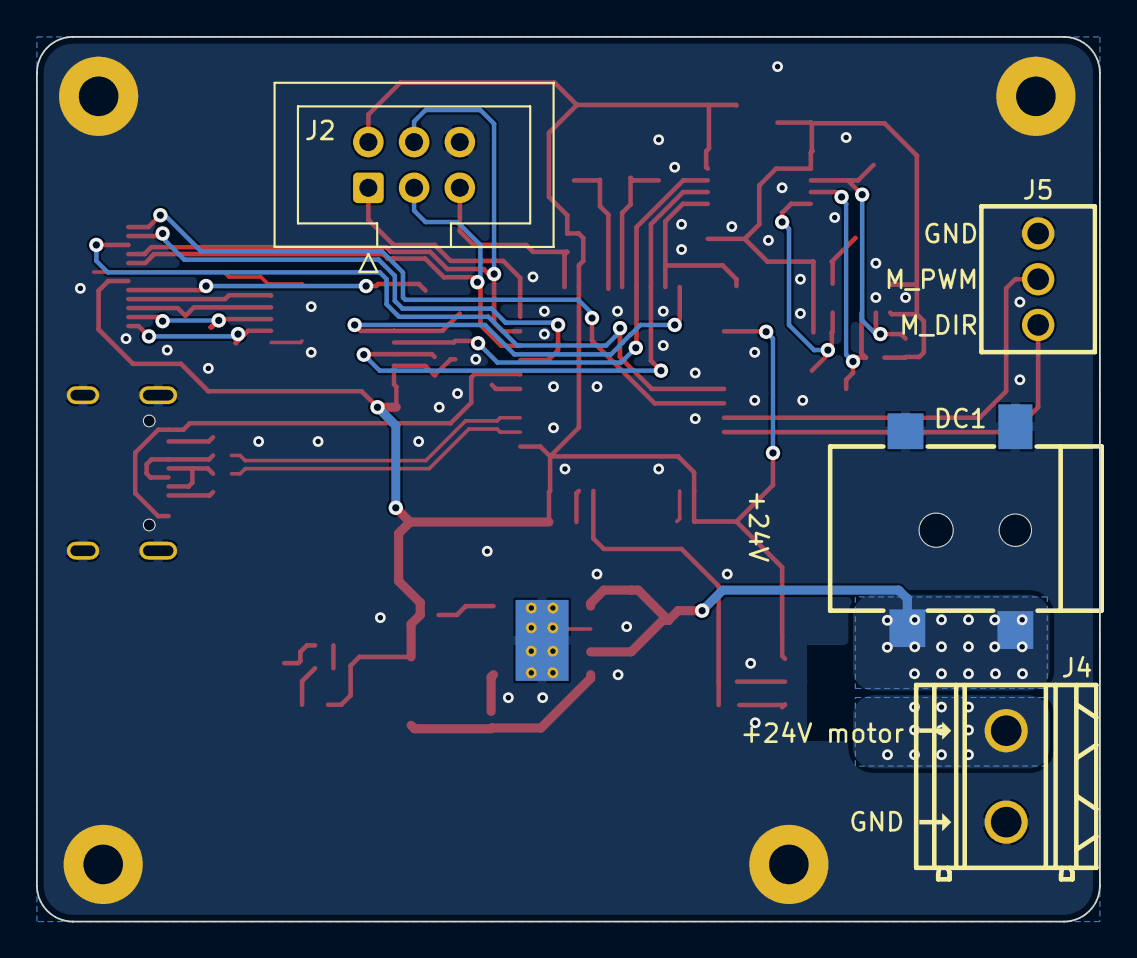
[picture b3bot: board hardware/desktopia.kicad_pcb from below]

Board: 2 copper layers, 59.1 x 49.1 mm, 76 parts (4 on the bottom side), 47 nets.

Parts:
C1: 10nF; C_0402_1005Metric
C2: 4.7uF; RVT1H4R7M0405_C18221489
C4: 33uF; VE-330M1A0505-TRO
C6, C7, C10, C12, C17, C18, C19, C20: 100nF; C_0402_1005Metric
C8, C9: 10pF; C_0402_1005Metric
C11, C13, C14, C15: 1uF; C_0402_1005Metric
C16: 4.7uF; C_0402_1005Metric
C21: 1nF; C_0402_1005Metric
C22: 100pF; C_0402_1005Metric
D1: SS14; D_SMA
DC1: DC050-2_5-T
FPC_MB1: F2D12U-A1G1-ER
H1, H1#2, H1#3, H2: MountingHole_Pad; MountingHole_2.2mm_M2_Pad
J2: Prog_Connector; IDC-Header_2x03_P2.54mm_Vertical
J3: USB4105GFA; GCT_USB4105GFA
J4: PowerMotor; C508128L-2P0G36
J5: MotorCommandCon; ZX-DG28L-2_54-3P
JP1: SolderJumper_2_Open; SolderJumper-2_P1.3mm_Open_TrianglePad1.0x1.5mm
L1: 84uH; L5.8
LED1: KT-0603R
R1, R2, R21: 100; R_0402_1005Metric
R3, R5, R10, R11, R12, R13, R14, R19, R20: 10k; R_0402_1005Metric
R4, R6, R7, R17, R18: 3.3k; R_0402_1005Metric
R8, R9: 22; R_0402_1005Metric
R15, R16: 5.1k; R_0402_1005Metric
RST1: SW_Push; DTS41
TP1, TP7, TP8, TP9, TP10, TP11, TP14, TP15, TP16, TP17, TP18, TP19: TestPoint; TestPoint_Pad_D1.0mm
U1: TPS5430DDA; TI_SO-PowerPAD-8_ThermalVias
U2: TCA9554DB; SSOP-16_5.3x6.2mm_P0.65mm
U3: ATmega32U4-A; TQFP-44_10x10mm_P0.8mm
U4: XC6206P282MR; SOT-23-3
U5: TXS0104EPW; TSSOP-14_4.4x5mm_P0.65mm
U6: VL53L1CBV0FY_1
U7: CC6905S8-5FB005; SOP-8_3.76x4.96mm_P1.27mm
Y1: X322516MLB4SI; Crystal_SMD_3225-4Pin_3.2x2.5mm

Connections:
+2V8: C15.2, C16.1, C17.1, C19.1, R17.1, R18.1, R19.1, R20.1, TP11.1 (1_1), U4.2 (Vout), U5.1 (V_{CCA}), U5.8 (OE), U6.1 (AVDDVCSEL), U6.11 (AVDD)
+5V: C4.1, C6.2, C7.2, C10.2, C11.2, C14.2, C18.1, C20.2, FPC_MB1.6, J2.2, JP1.1 (A), L1.2, R3.1, R5.1, R6.1, R7.1, TP10.1 (1_1), U2.16 (VDD), U3.2 (UVCC), U3.14 (VCC), U3.24 (AVCC), U3.34 (VCC), U3.44 (AVCC), U4.3 (Vin), U5.14 (V_{CCB}), U7.8 (VCC)
+24V: C2.1, DC1.4, TP1.1 (1_1), U1.5 (EN), U1.7 (VIN), U7.1 (IP+), U7.2 (IP+)
/CS_MBside: FPC_MB1.11, U3.8 (PB0)
/D+: R8.2, U3.4 (D+)
/D-: R9.2, U3.3 (D-)
/DC_MBside: FPC_MB1.10, U3.28 (PB4)
/GPIO1_VL53: TP14.1 (1_1), U3.20 (PD2), U5.11 (B3)
/HMI_~INT: TP8.1 (1_1), U2.13 (~INT), U3.21 (PD3)
/Imotor: C22.2, R21.2, TP19.1 (1_1), U3.41 (PF0)
/MISO: J2.1, U3.11 (PB3)
/MOSI: FPC_MB1.9, J2.4, U3.10 (PB2)
/Mdir: J5.1, U3.31 (PC6)
/Mpwm: J5.2, U3.30 (PB6)
/RESET: J2.5, R5.2, RST1.2, TP7.1 (1_1), U3.13 (~RESET)
/RST_MBside: FPC_MB1.12, U3.29 (PB5)
/SCK: FPC_MB1.8, J2.3, U3.9 (PB1)
/SCL: R6.2, U2.14 (SCL), U3.18 (PD0), U5.13 (B1)
/SDA: R7.2, U2.15 (SDA), U3.19 (PD1), U5.12 (B2)
/SW1_MBside: FPC_MB1.1, R10.1, U2.4 (P0)
/SW2_MBside: FPC_MB1.2, R11.1, U2.5 (P1)
/SW3_MBside: FPC_MB1.3, R12.1, U2.6 (P2)
/SW4_MBside: FPC_MB1.4, R13.1, U2.7 (P3)
/SW5_MBside: FPC_MB1.5, R14.1, U2.9 (P4)
GND: C2.2, C4.2, C6.1, C7.1, C8.1, C9.1, C10.1, C11.1, C12.1, C13.1, C14.1, C15.1, C16.2, C17.2, C18.2, C19.2, C20.1, C21.1, C22.1, D1.2 (A), DC1.2, DC1.3, FPC_MB1.7, FPC_MB1.13, FPC_MB1.14, H1.1 (1_1), H1#2.1 (1_1), H1#3.1 (1_1), H2.1 (1_1), J2.6, J3.A1_B12 (GND), J3.B1_A12 (GND), J3.SH1 (SHELL_GND), J3.SH2 (SHELL_GND), J3.SH3 (SHELL_GND), J3.SH4 (SHELL_GND), J4.2, J5.3, LED1.2 (K), R4.2, R10.2, R11.2, R12.2, R13.2, R14.2, R15.2, R16.2, RST1.1, TP9.1 (1_1), U1.6 (GND), U1.9 (GNDPAD), U2.1 (A0), U2.2 (A1), U2.3 (A2), U2.8 (GND), U3.5 (UGND), U3.15 (GND), U3.23 (GND), U3.33 (~HWB/PE2), U3.35 (GND), U3.43 (GND), U4.1 (GND), U5.7 (GND), U6.2 (AVSSVCSEL), U6.3 (GND), U6.4 (GND2), U6.6 (GND3), U6.12 (GND4), U7.5 (GND), Y1.2 (G), Y1.3 (G)
unnamed: C1.1, D1.1 (K), L1.1, U1.8 (PH)
unnamed: J3.A5 (CC1), R16.1
unnamed: J3.B5 (CC2), R15.1
unnamed: J3.A7 (DN1), J3.B7 (DN2), R9.1
unnamed: J3.A6 (DP1), J3.B6 (DP2), R8.1
unnamed: J4.1, U7.3 (IP-), U7.4 (IP-)
unnamed: JP1.2 (B), R1.1
unnamed: LED1.1 (A), R2.2
unnamed: R1.2, R2.1
unnamed: C1.2, U1.1 (BOOT)
unnamed: R3.2, R4.1, U1.4 (VSENSE)
unnamed: C12.2, U3.42 (AREF)
unnamed: C13.2, U3.6 (UCAP)
unnamed: C8.2, U3.17 (XTAL1), Y1.4
unnamed: C9.2, U3.16 (XTAL2), Y1.1
unnamed: R17.2, TP15.1 (1_1), U5.2 (A1), U6.10 (SCL)
unnamed: R18.2, TP16.1 (1_1), U5.3 (A2), U6.9 (SDA)
unnamed: R20.2, TP17.1 (1_1), U5.4 (A3), U6.7 (GPIO1)
unnamed: R19.2, TP18.1 (1_1), U6.5 (XSHUT)
unnamed: R21.1, U7.7 (VOUT)
unnamed: C21.2, U7.6 (VREF)
VBUS: J3.A4_B9 (VBUS), J3.B4_A9 (VBUS), U3.7 (VBUS)
